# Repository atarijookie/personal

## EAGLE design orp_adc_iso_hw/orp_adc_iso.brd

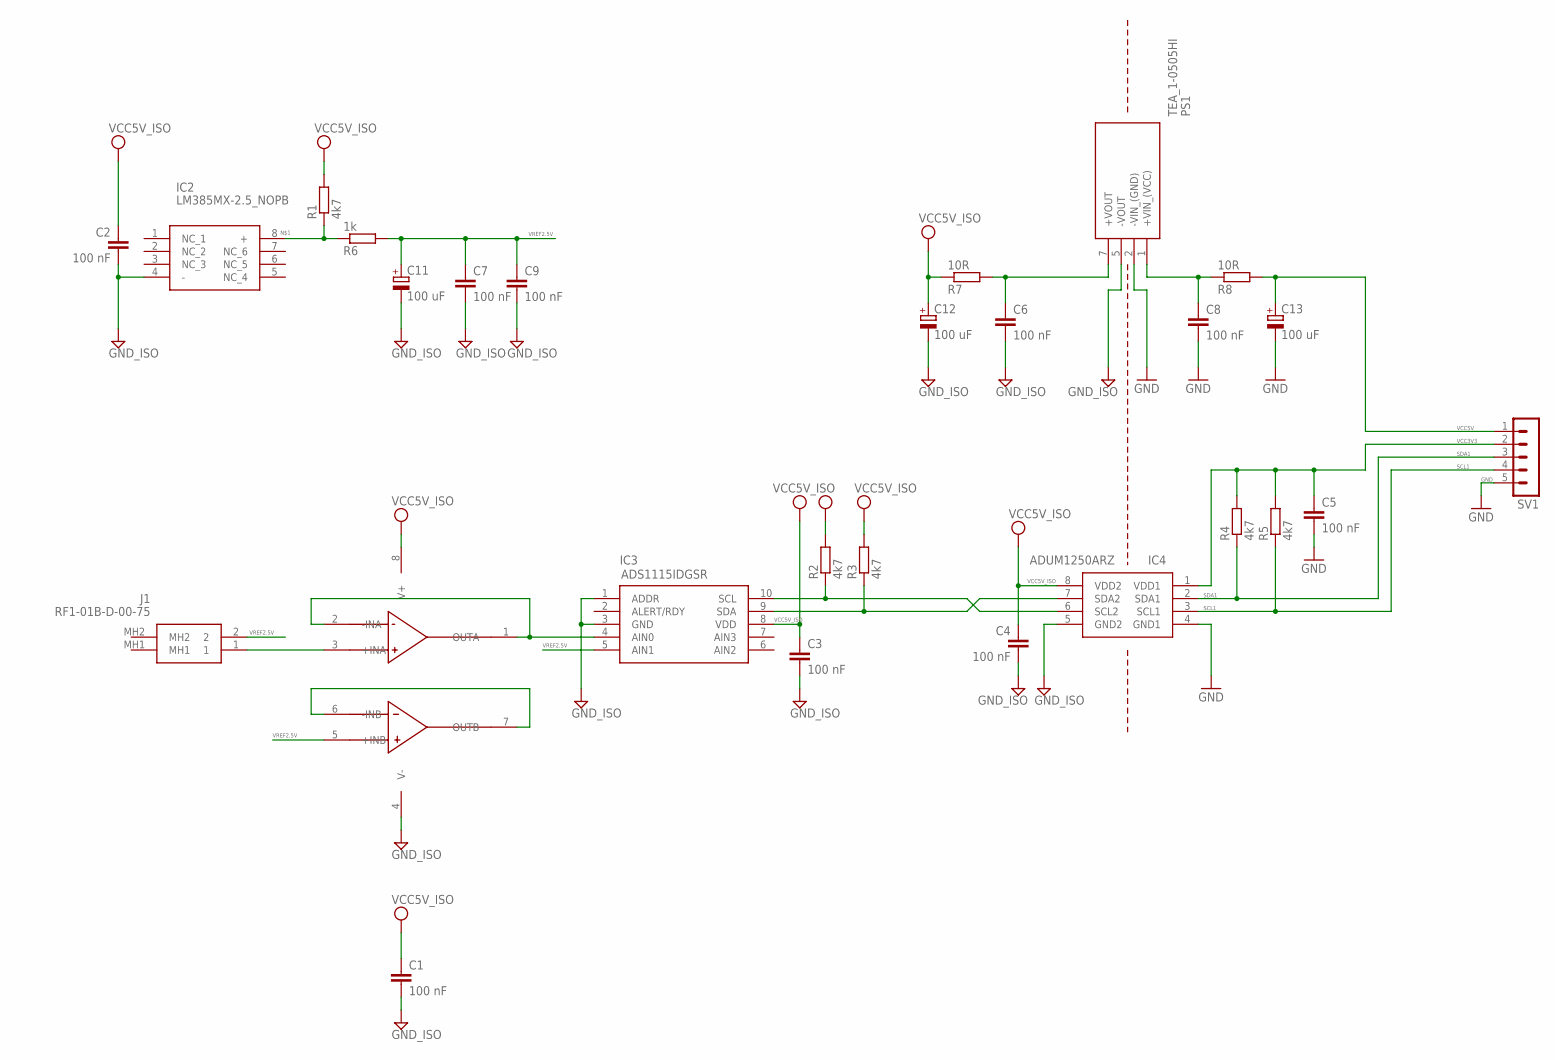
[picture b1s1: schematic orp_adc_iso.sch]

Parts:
C1, C2, C3, C4, C5, C6, C7, C8, C9: 100 nF; C0603
C11, C12, C13: 100 uF; SMC_C
IC2: LM385MX-2.5_NOPB; SOIC127P600X175-8N
IC3: ADS1115IDGSR; SOP50P490X110-10N
IC4: ADUM1250ARZ; SOIC127P600X175-8N
J1: RF1-01B-D-00-75; RF101BD0075
PS1: TEA_1-0505HI; TEA10505HI
R1, R2, R3, R4, R5: 4k7; R0603
R6: 1k; R0603
R7, R8: 10R; R0603
SV1: MA05-1
U$1: LMC6482AIMX/NOPB; SO8

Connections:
GND: C5.2, C8.2, C13.-, IC4.4 (GND1), PS1.2 (-VIN_(GND)), SV1.5
GND_ISO: C1.2, C2.2, C3.2, C4.2, C6.2, C7.2, C9.2, C11.-, C12.-, IC2.4 (-), IC3.1 (ADDR), IC3.3 (GND), IC4.5 (GND2), PS1.5 (-VOUT), U$1.4 (V-)
unnamed: IC2.8 (+), R1.1, R6.1
unnamed: J1.1, U$1.3 (+INA)
unnamed: IC3.4 (AIN0), U$1.1 (OUTA), U$1.2 (-INA)
unnamed: U$1.6 (-INB), U$1.7 (OUTB)
unnamed: IC3.9 (SDA), IC4.7 (SDA2), R3.1
unnamed: IC3.10 (SCL), IC4.6 (SCL2), R2.1
SCL1: IC4.3 (SCL1), R5.1, SV1.4
SDA1: IC4.2 (SDA1), R4.1, SV1.3
VCC3V3: C5.1, IC4.1 (VDD1), R4.2, R5.2, SV1.2
VCC5V: C13.+, R8.2, SV1.1
VCC5V_INTERNAL: C8.1, PS1.1 (+VIN_(VCC)), R8.1
VCC5V_ISO: C1.1, C2.1, C3.1, C4.1, C12.+, IC3.8 (VDD), IC4.8 (VDD2), R1.2, R2.2, R3.2, R7.1, U$1.8 (V+)
VCC5V_ISO_INTERNAL: C6.1, PS1.7 (+VOUT), R7.2
VREF2.5V: C7.1, C9.1, C11.+, IC3.5 (AIN1), J1.2, R6.2, U$1.5 (+INB)

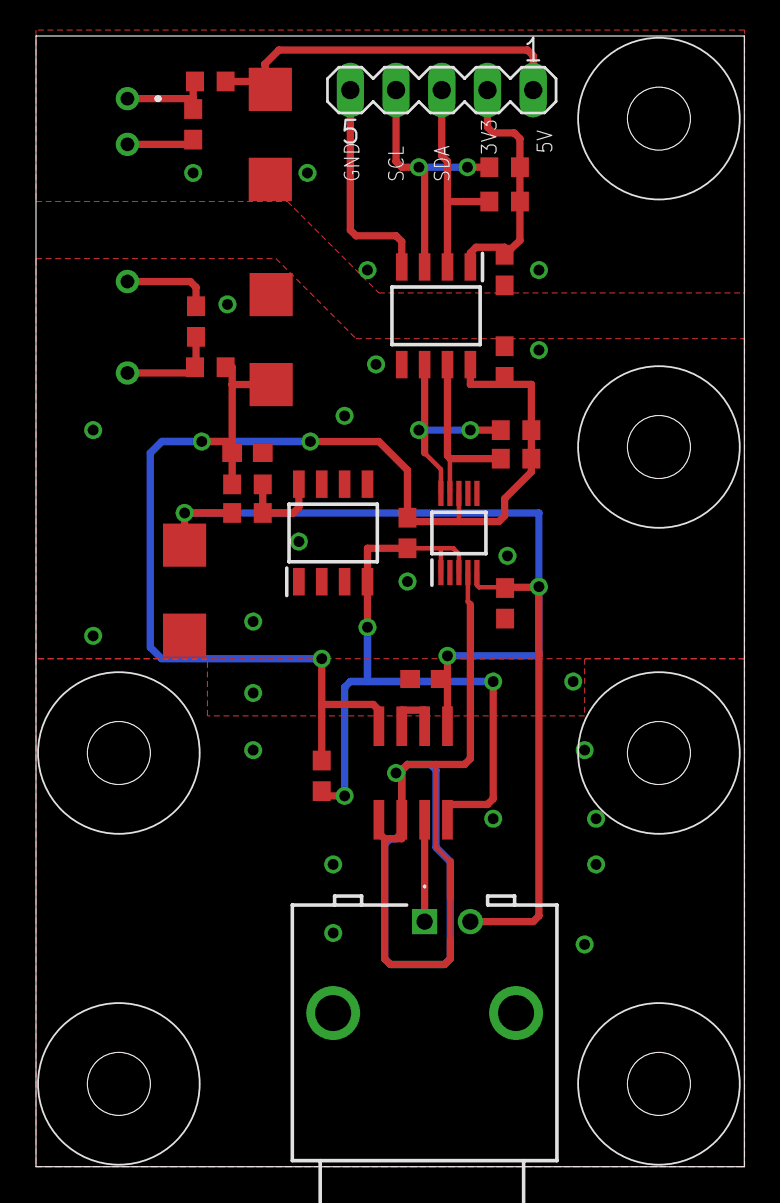
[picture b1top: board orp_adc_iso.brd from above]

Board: 2 copper layers, 39.3 x 62.8 mm, 27 parts (0 on the bottom side), 16 nets.

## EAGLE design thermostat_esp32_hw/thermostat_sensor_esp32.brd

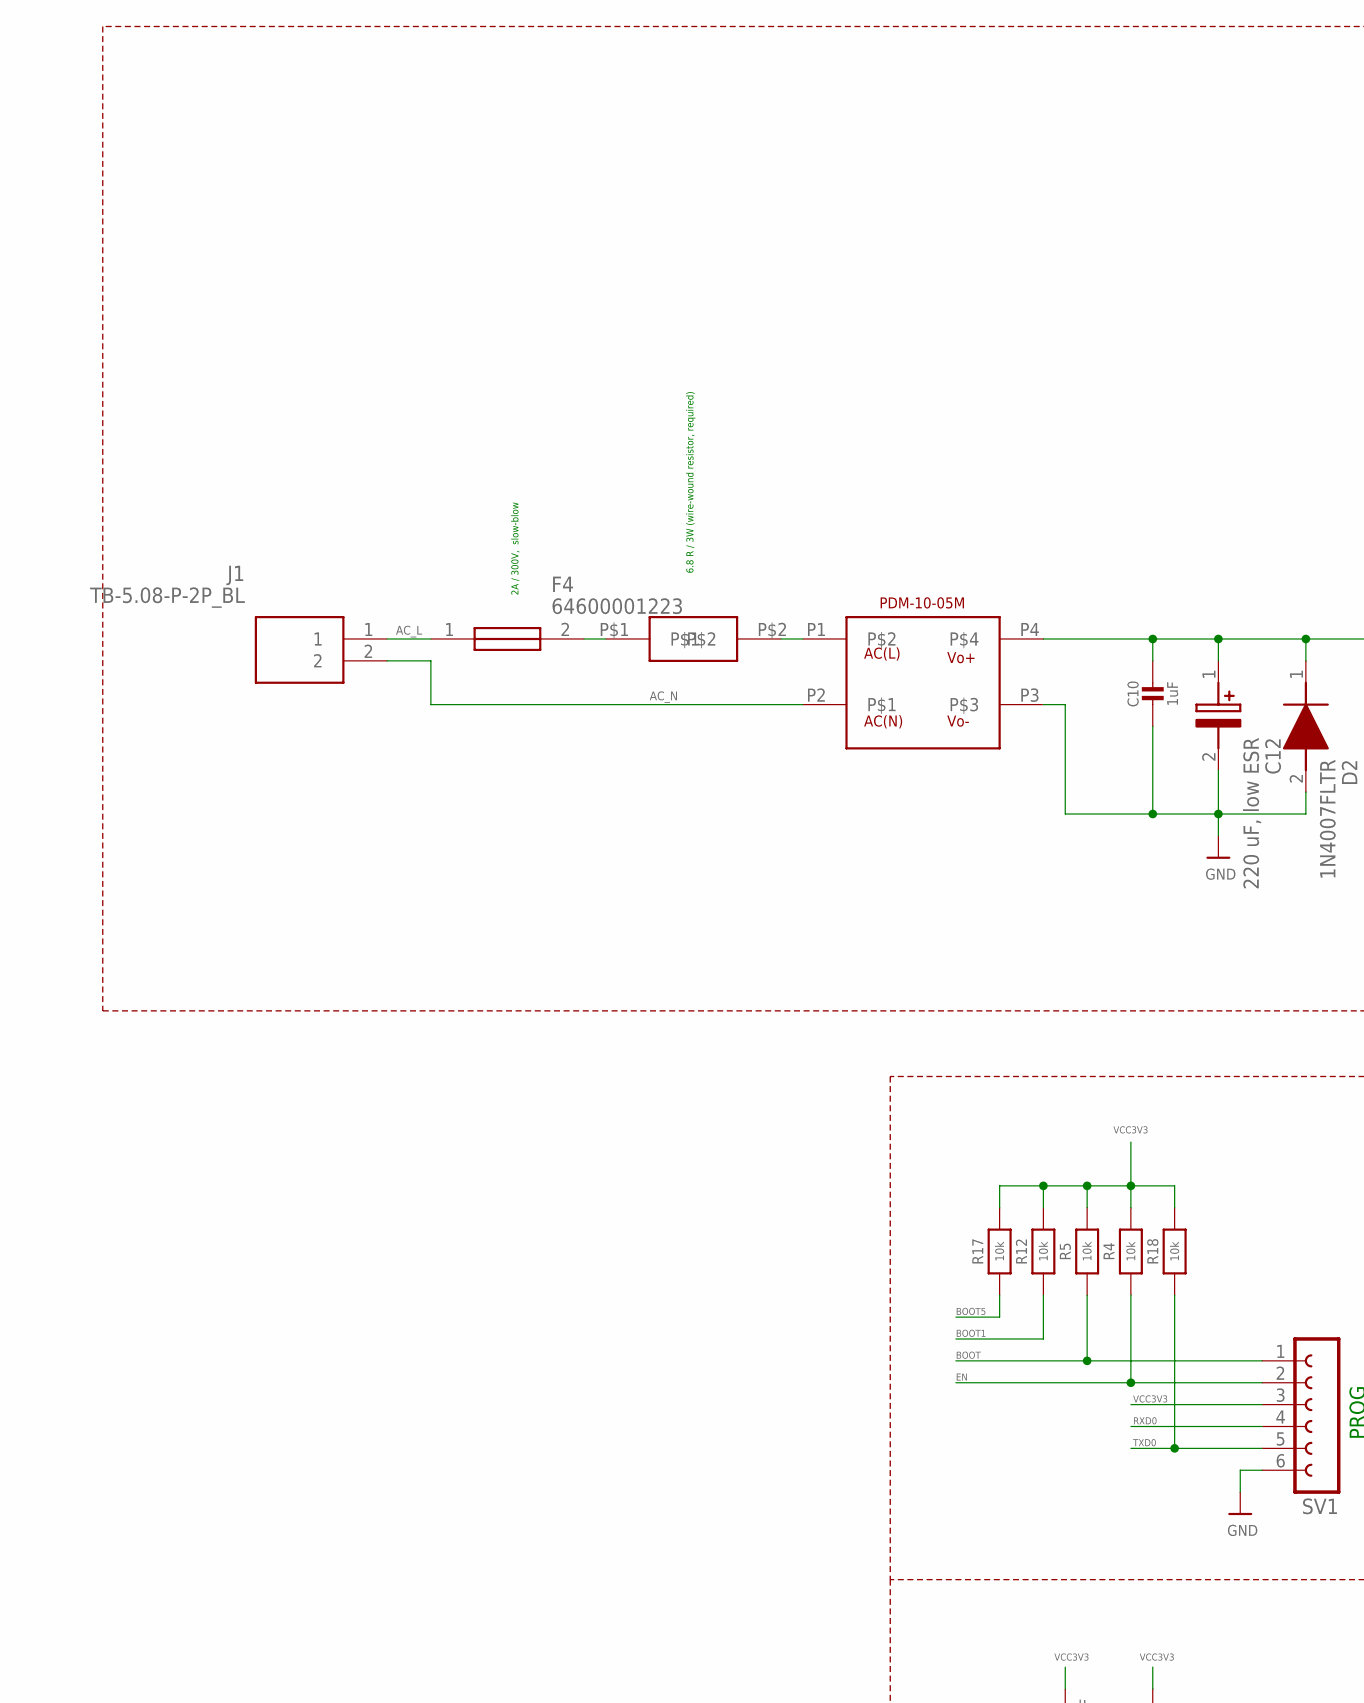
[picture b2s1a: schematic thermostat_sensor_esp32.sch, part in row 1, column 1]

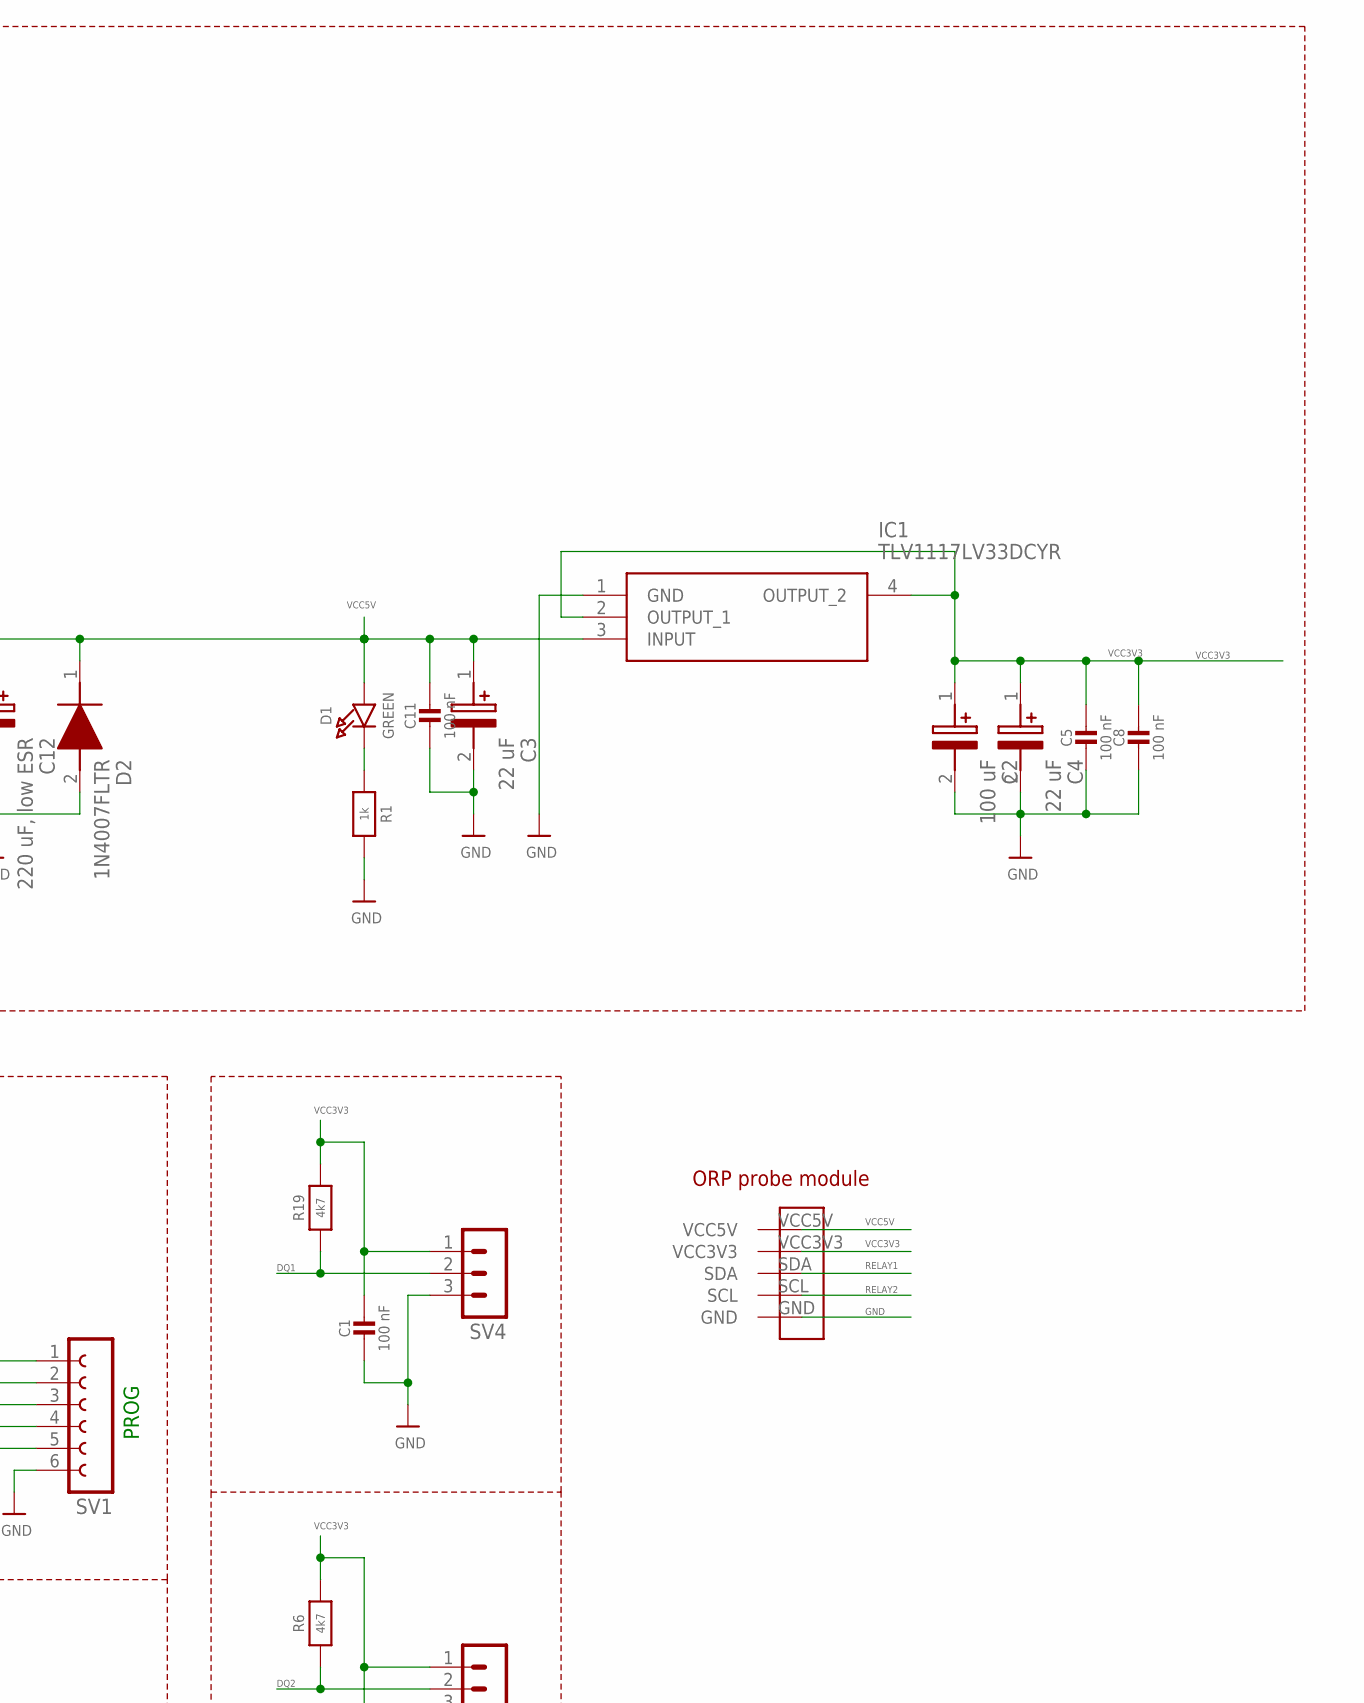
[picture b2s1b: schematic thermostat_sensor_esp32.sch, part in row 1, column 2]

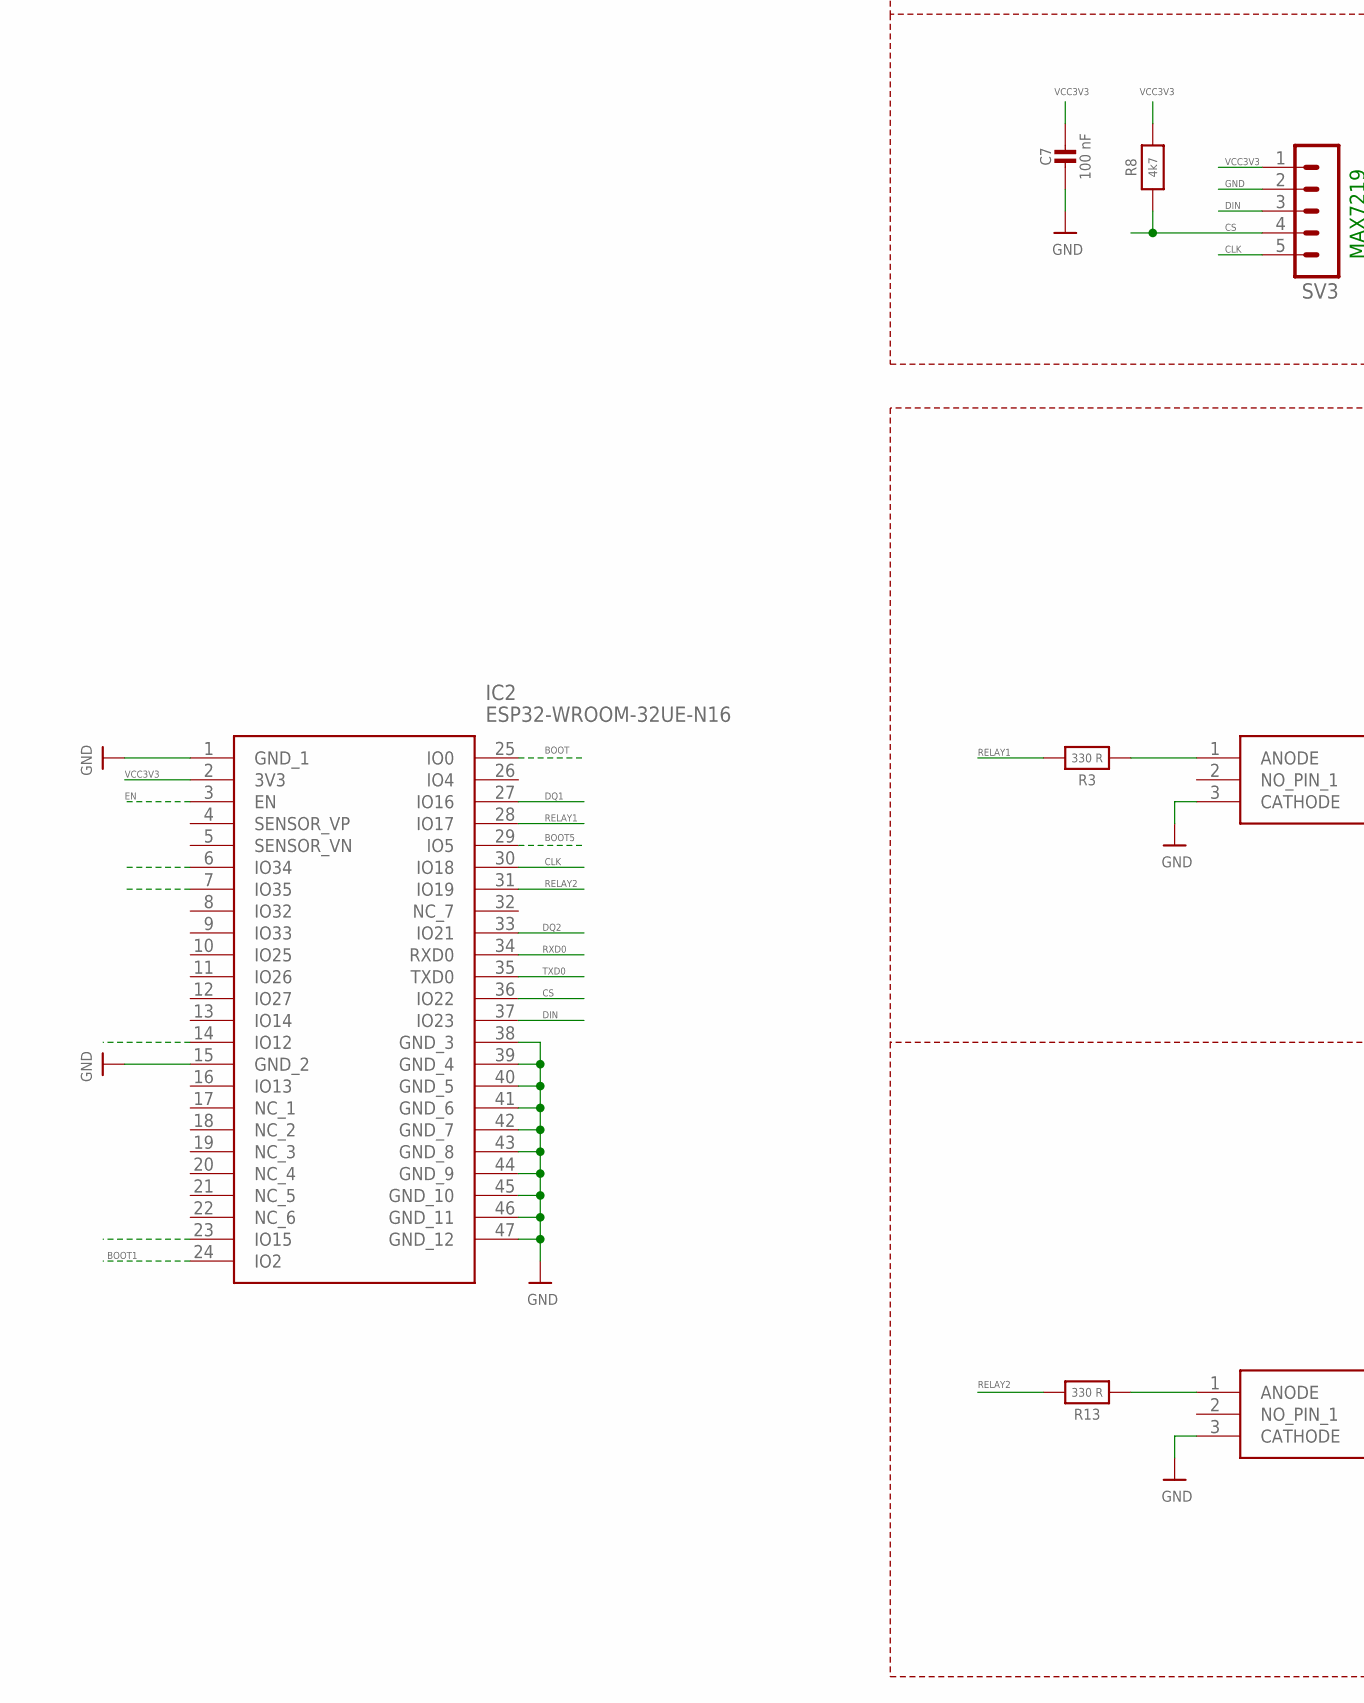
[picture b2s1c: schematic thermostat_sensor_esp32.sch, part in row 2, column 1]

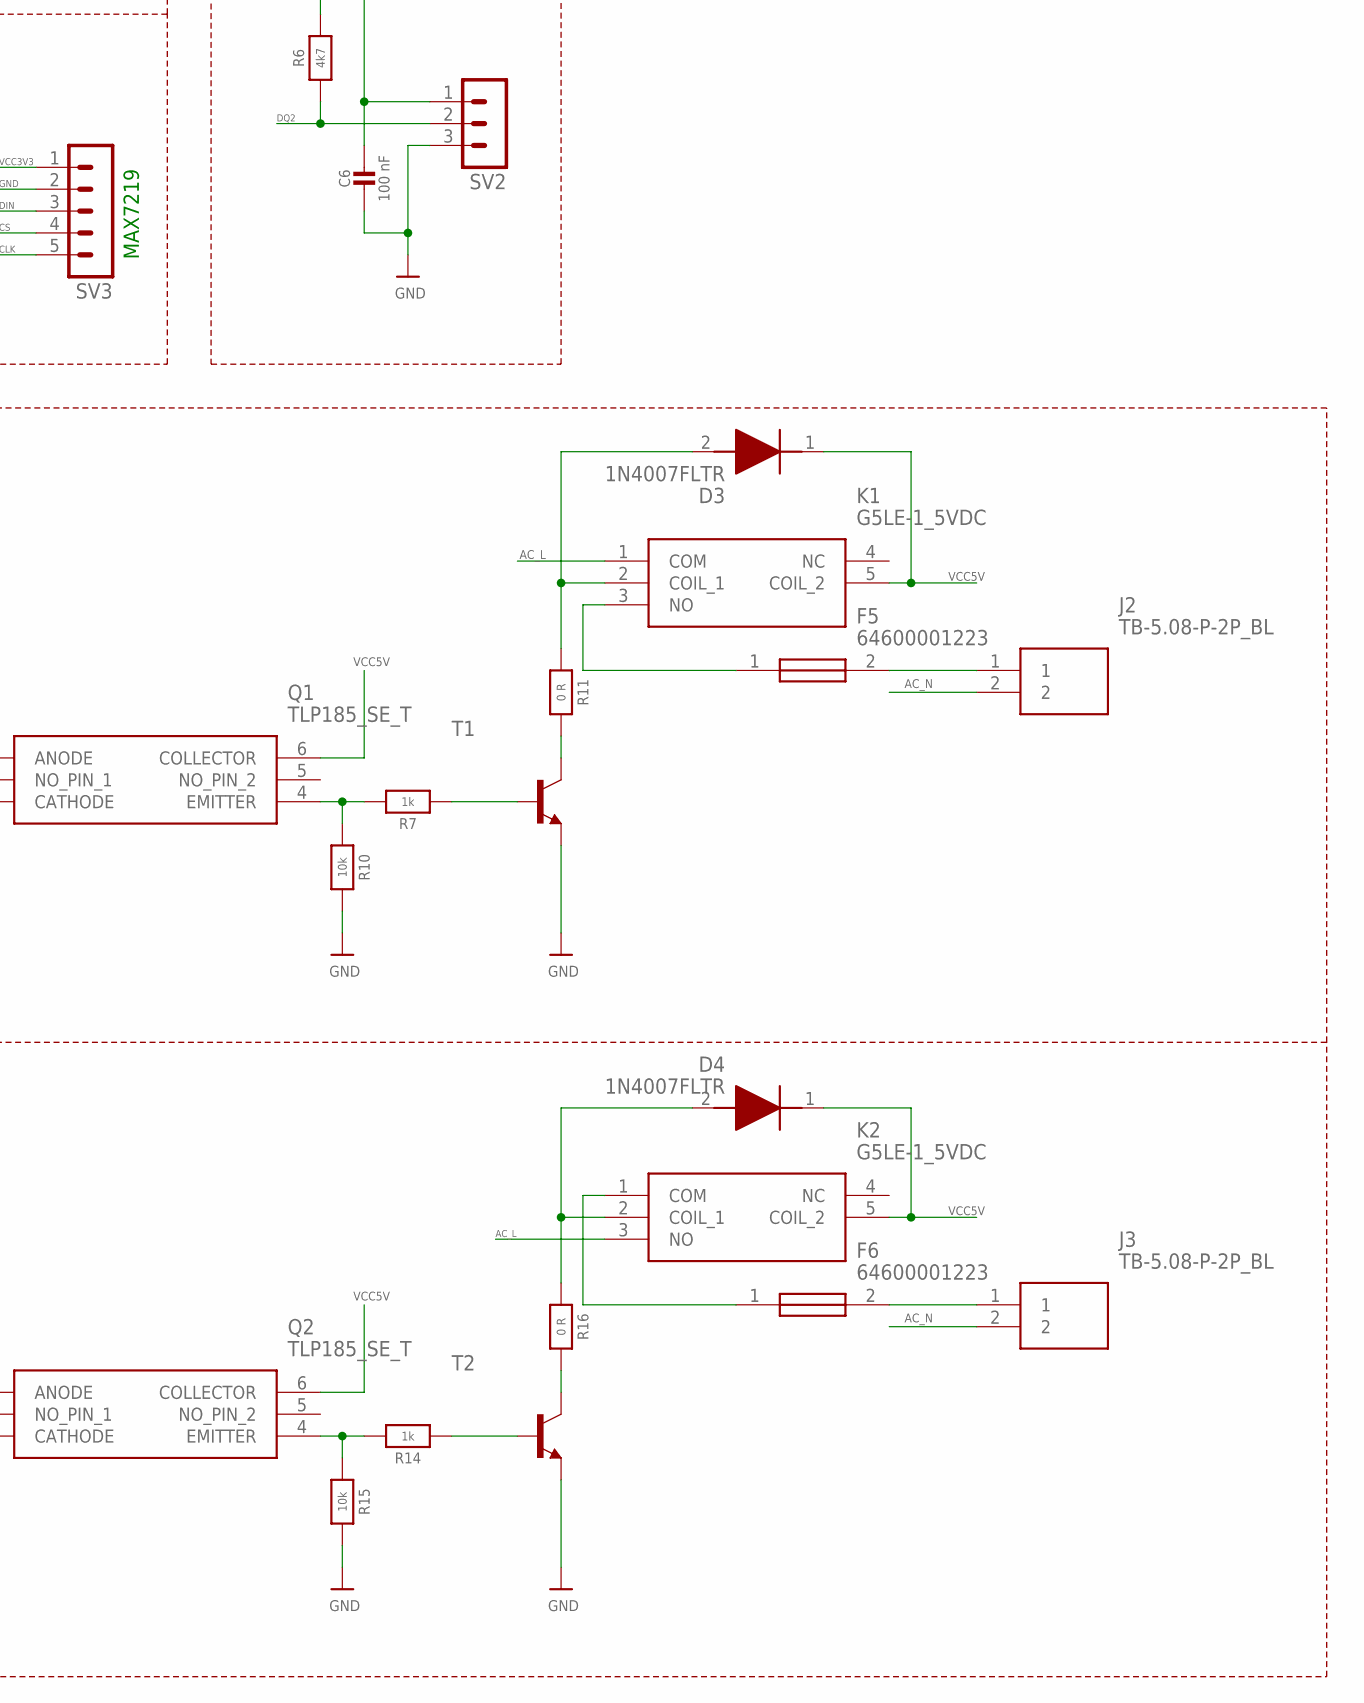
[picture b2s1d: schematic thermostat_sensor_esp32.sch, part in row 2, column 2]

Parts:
C1, C5, C6, C7, C8, C11: 100 nF; _0603
C2: 100 uF; CAPPM6032X280N
C3, C4: 22 uF; CAPPM3216X180N; MANUFACTURER_PART_NUMBER 293D226X9010A2TE3
C10: 1uF; 0805-NO
C12: 220 uF, low ESR; CAPPRD350W65D800H1300
D1: GREEN; CHIPLED_0805_NOOUTLINE
D2: 1N4007FLTR; SODFL3718X140N
D3, D4: 1N4007FLTR; SODFL3718X140N; MANUFACTURER_PART_NUMBER 1N4007FLTR
F4, F5, F6: 64600001223
IC1: TLV1117LV33DCYR; SOT230P700X180-4N
IC2: ESP32-WROOM-32UE-N16; ESP32WROOM32UEN16
J1: TB-5.08-P-2P_BL; TB508P2PBL
J2, J3: TB-5.08-P-2P_BL; TB508P2PBL; MANUFACTURER_PART_NUMBER TB-5.08-P-2P/BL
K1, K2: G5LE-1_5VDC; G5LE15VDC
Q1, Q2: TLP185_SE_T; SOIC127P700X230-6N
R1, R7, R14: 1k; _0603
R3, R13: 330 R; _0603
R4, R5, R10, R12, R15, R17, R18: 10k; _0603
R6, R8, R19: 4k7; _0603
R11, R16: 0 R; _0603
SV1: FE06-1; FE06
SV2, SV4: MA03-1
SV3: MA05-1
T1, T2: BC817-16-NPN-SOT23-BEC; SOT23-BEC
U$1: PDM-10-05M
U$20: 6.8 R / 3W (wire-wound resistor, required); R_HIGH_POWER
U$21: ORP_PROBE

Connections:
AC_L: F4.1, J1.1, K1.1 (COM), K2.3 (NO)
AC_N: J1.2, J2.2, J3.2, U$1.P2
BOOT: IC2.25 (IO0), R5.1, SV1.1
BOOT1: IC2.24 (IO2), R12.1
BOOT5: IC2.29 (IO5), R17.1
CLK: IC2.30 (IO18), SV3.5
CS: IC2.36 (IO22), R8.1, SV3.4
DIN: IC2.37 (IO23), SV3.3
DQ1: IC2.27 (IO16), R19.1, SV4.2
DQ2: IC2.33 (IO21), R6.1, SV2.2
EN: IC2.3 (EN), R4.1, SV1.2
GND: C1.2, C2.2 (-), C3.2 (-), C4.2 (-), C5.2, C6.2, C7.2, C8.2, C10.2, C11.2, C12.2 (-), D2.2 (A), IC1.1 (GND), IC2.1 (GND_1), IC2.15 (GND_2), IC2.38 (GND_3), IC2.39 (GND_4), IC2.40 (GND_5), IC2.41 (GND_6), IC2.42 (GND_7), IC2.43 (GND_8), IC2.44 (GND_9), IC2.45 (GND_10), IC2.46 (GND_11), IC2.47 (GND_12), Q1.3 (CATHODE), Q2.3 (CATHODE), R1.2, R10.2, R15.2, SV1.6, SV2.3, SV3.2, SV4.3, T1.E, T2.E, U$1.P3, U$21.GND
unnamed: Q2.1 (ANODE), R13.1
unnamed: F5.1, K1.3 (NO)
unnamed: D1.C, R1.1
unnamed: U$1.P1, U$20.P$2
unnamed: F5.2, J2.1
unnamed: Q1.1 (ANODE), R3.1
unnamed: Q1.4 (EMITTER), R7.2, R10.1
unnamed: R7.1, T1.B
unnamed: R11.2, T1.C
unnamed: D3.2 (A), K1.2 (COIL_1), R11.1
unnamed: Q2.4 (EMITTER), R14.2, R15.1
unnamed: R14.1, T2.B
unnamed: R16.2, T2.C
unnamed: D4.2 (A), K2.2 (COIL_1), R16.1
unnamed: F6.1, K2.1 (COM)
unnamed: F6.2, J3.1
unnamed: F4.2, U$20.P$1
RELAY1: IC2.28 (IO17), R3.2, U$21.SDA
RELAY2: IC2.31 (IO19), R13.2, U$21.SCL
RXD0: IC2.34 (RXD0), SV1.4
TXD0: IC2.35 (TXD0), R18.1, SV1.5
VCC3V3: C1.1, C2.1 (+), C4.1 (+), C5.1, C6.1, C7.1, C8.1, IC1.2 (OUTPUT_1), IC1.4 (OUTPUT_2), IC2.2 (3V3), R4.2, R5.2, R6.2, R8.2, R12.2, R17.2, R18.2, R19.2, SV1.3, SV2.1, SV3.1, SV4.1, U$21.VCC3V3
VCC5V: C3.1 (+), C10.1, C11.1, C12.1 (+), D1.A, D2.1 (K), D3.1 (K), D4.1 (K), IC1.3 (INPUT), K1.5 (COIL_2), K2.5 (COIL_2), Q1.6 (COLLECTOR), Q2.6 (COLLECTOR), U$1.P4, U$21.VCC5V

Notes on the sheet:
2A / 300V, slow-blow
6.8 R / 3W (wire-wound resistor, required)
MAX7219
PROG
ORP probe module

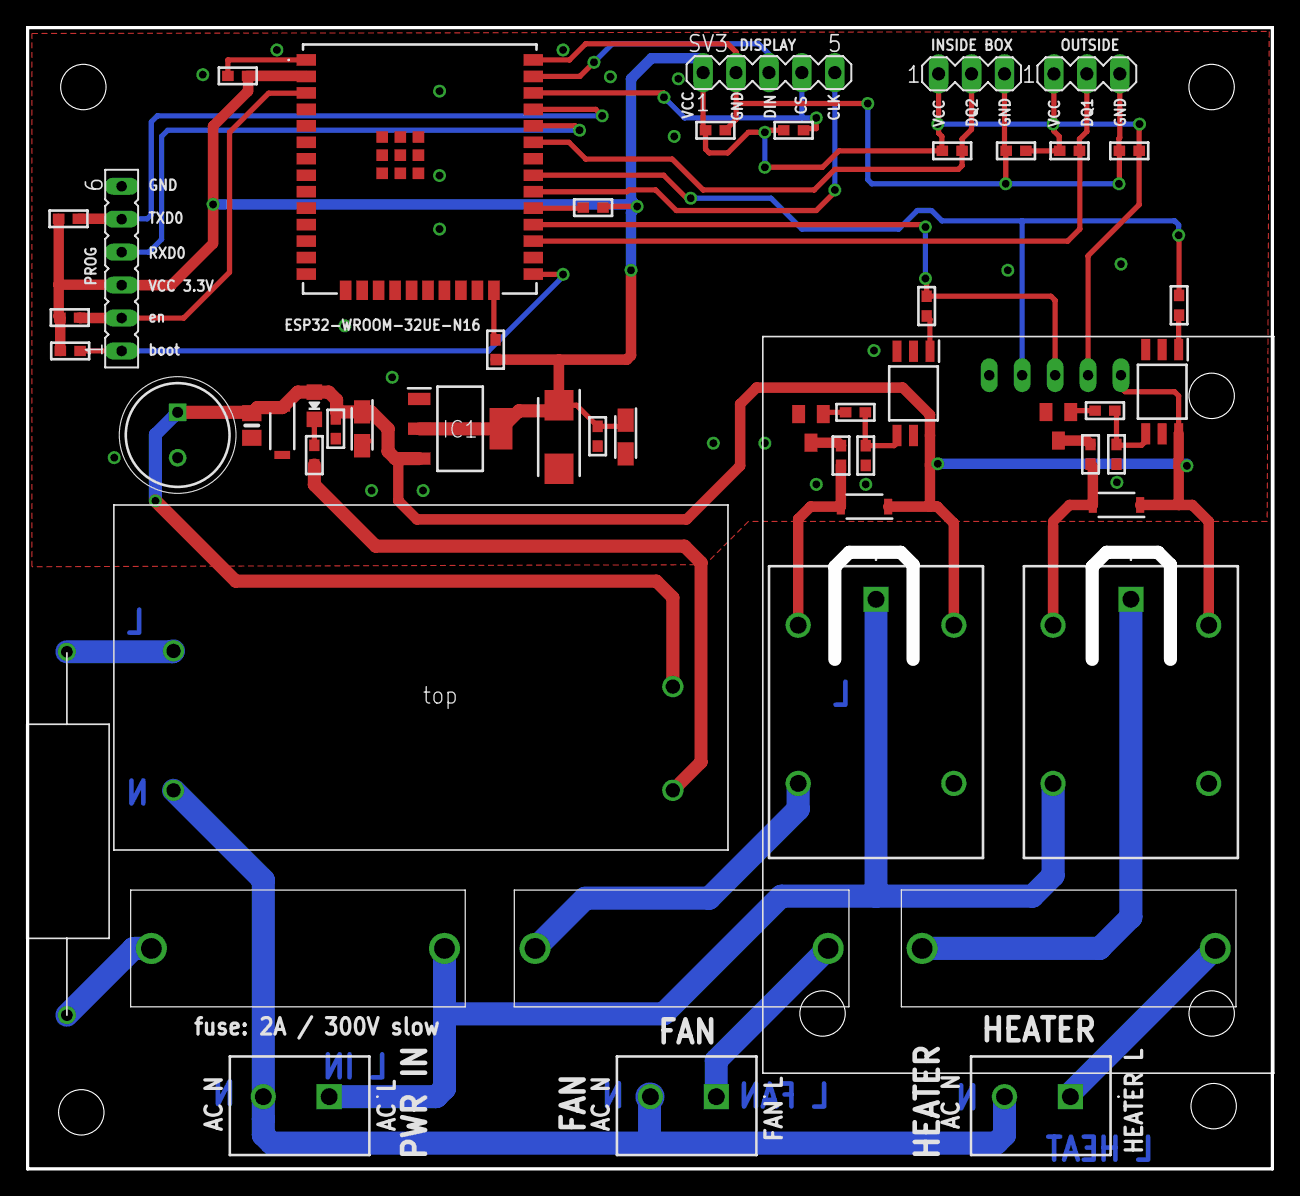
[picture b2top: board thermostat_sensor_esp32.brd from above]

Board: 2 copper layers, 95.2 x 87.2 mm, 53 parts (1 on the bottom side), 35 nets.
